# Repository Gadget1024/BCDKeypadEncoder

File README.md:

# BCDKeypadEncoder
 BCD Keypad encoder for Roger Hampson

Hardware and Software by Rob Barter (Bedrock Systems Limited)

KiCAD schematics and PCB Layout
Micro PIC16F1847 C++ Code

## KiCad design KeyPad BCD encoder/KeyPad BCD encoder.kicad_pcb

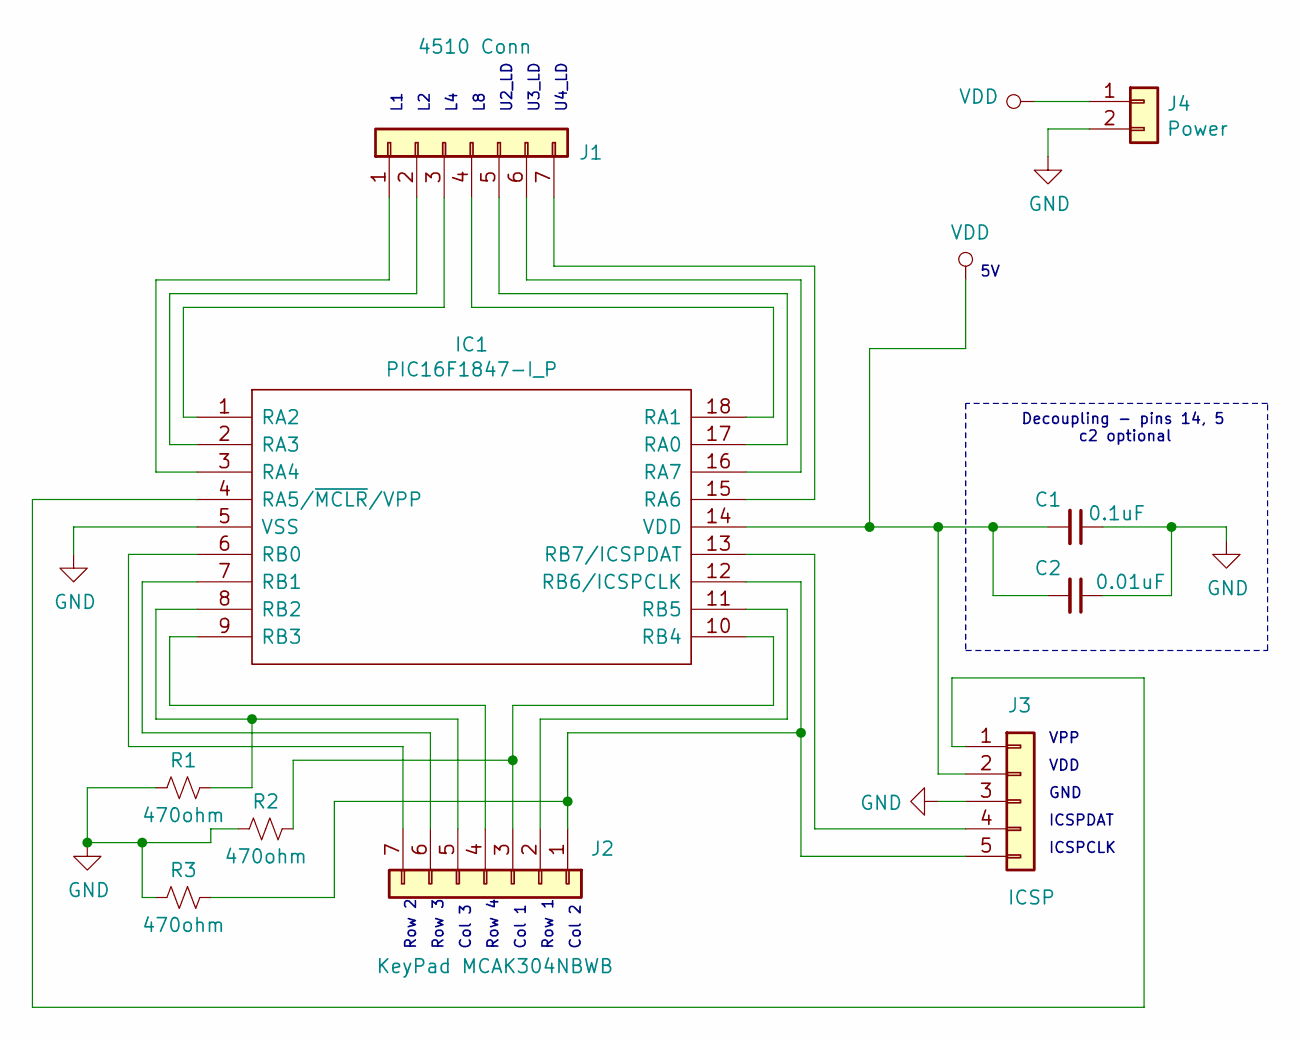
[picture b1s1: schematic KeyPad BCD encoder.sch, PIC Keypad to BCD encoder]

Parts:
C1: 0.1uF; C_1206_3216Metric_Pad1.42x1.75mm_HandSolder
C2: 0.01uF; C_1206_3216Metric_Pad1.42x1.75mm_HandSolder
IC1: PIC16F1847-I_P; SOIC-18W_7.5x11.6mm_P1.27mm; Mouser Part Number 579-PIC16F1847-I/P
J1: 4510 Conn; PinHeader_1x07_P2.54mm_Vertical
J2: KeyPad MCAK304NBWB; PinHeader_1x07_P2.54mm_Vertical
J3: ICSP; PinHeader_1x05_P2.54mm_Vertical
J4: Power; PinHeader_1x02_P2.54mm_Vertical
R1, R2, R3: 470ohm; R_0805_2012Metric_Pad1.15x1.40mm_HandSolder

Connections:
GND: C1.1, C2.1, IC1.5 (VSS), J3.3, J4.2, R1.2, R2.2, R3.2
unnamed: IC1.1 (RA2), J1.3
unnamed: IC1.2 (RA3), J1.2
unnamed: IC1.3 (RA4), J1.1
unnamed: IC1.4 (RA5/~MCLR~/VPP), J3.1
unnamed: IC1.6 (RB0), J2.7
unnamed: IC1.7 (RB1), J2.6
unnamed: IC1.8 (RB2), J2.5, R1.1
unnamed: IC1.9 (RB3), J2.4
unnamed: IC1.10 (RB4), J2.3, R2.1
unnamed: IC1.11 (RB5), J2.2
unnamed: IC1.12 (RB6/ICSPCLK), J2.1, J3.5, R3.1
unnamed: IC1.13 (RB7/ICSPDAT), J3.4
unnamed: IC1.15 (RA6), J1.7
unnamed: IC1.16 (RA7), J1.6
unnamed: IC1.17 (RA0), J1.5
unnamed: IC1.18 (RA1), J1.4
VDD: C1.2, C2.2, IC1.14 (VDD), J3.2, J4.1

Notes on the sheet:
Col 2
Row 1
Col 1
Row 4
Col 3
Row 3
Row 2
U4_LD
U3_LD
U2_LD
VPP
VDD
GND
ICSPDAT
ICSPCLK
Decoupling - pins 14, 5 c2 optional

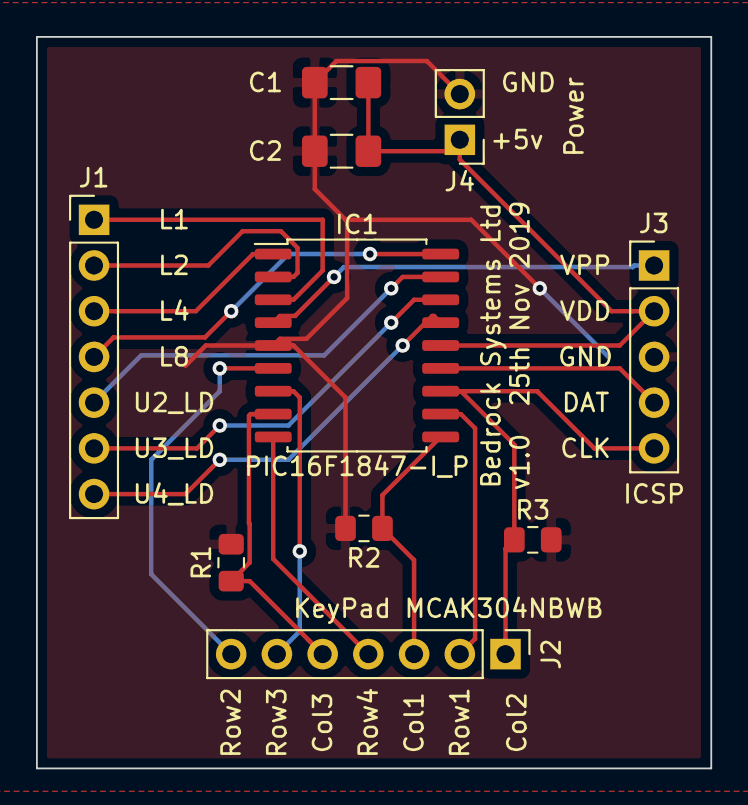
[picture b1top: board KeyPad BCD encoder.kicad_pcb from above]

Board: 2 copper layers, 37.5 x 40.6 mm, 10 parts (0 on the bottom side), 18 nets.

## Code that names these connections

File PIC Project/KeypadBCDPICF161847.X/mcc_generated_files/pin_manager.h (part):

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// get/set U2_LD_4510 aliases
#define U2_LD_4510_TRIS                 TRISAbits.TRISA0
#define U2_LD_4510_LAT                  LATAbits.LATA0
#define U2_LD_4510_PORT                 PORTAbits.RA0
#define U2_LD_4510_ANS                  ANSELAbits.ANSA0
#define U2_LD_4510_SetHigh()            do { LATAbits.LATA0 = 1; } while(0)
#define U2_LD_4510_SetLow()             do { LATAbits.LATA0 = 0; } while(0)
#define U2_LD_4510_Toggle()             do { LATAbits.LATA0 = ~LATAbits.LATA0; } while(0)
#define U2_LD_4510_GetValue()           PORTAbits.RA0
#define U2_LD_4510_SetDigitalInput()    do { TRISAbits.TRISA0 = 1; } while(0)
#define U2_LD_4510_SetDigitalOutput()   do { TRISAbits.TRISA0 = 0; } while(0)
#define U2_LD_4510_SetAnalogMode()      do { ANSELAbits.ANSA0 = 1; } while(0)
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// get/set L8_4510 aliases
#define L8_4510_TRIS                 TRISAbits.TRISA1
#define L8_4510_LAT                  LATAbits.LATA1
#define L8_4510_PORT                 PORTAbits.RA1
#define L8_4510_ANS                  ANSELAbits.ANSA1
#define L8_4510_SetHigh()            do { LATAbits.LATA1 = 1; } while(0)
#define L8_4510_SetLow()             do { LATAbits.LATA1 = 0; } while(0)
#define L8_4510_Toggle()             do { LATAbits.LATA1 = ~LATAbits.LATA1; } while(0)
#define L8_4510_GetValue()           PORTAbits.RA1
#define L8_4510_SetDigitalInput()    do { TRISAbits.TRISA1 = 1; } while(0)
#define L8_4510_SetDigitalOutput()   do { TRISAbits.TRISA1 = 0; } while(0)
#define L8_4510_SetAnalogMode()      do { ANSELAbits.ANSA1 = 1; } while(0)
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// get/set L4_4510 aliases
#define L4_4510_TRIS                 TRISAbits.TRISA2
#define L4_4510_LAT                  LATAbits.LATA2
#define L4_4510_PORT                 PORTAbits.RA2
#define L4_4510_ANS                  ANSELAbits.ANSA2
#define L4_4510_SetHigh()            do { LATAbits.LATA2 = 1; } while(0)
#define L4_4510_SetLow()             do { LATAbits.LATA2 = 0; } while(0)
#define L4_4510_Toggle()             do { LATAbits.LATA2 = ~LATAbits.LATA2; } while(0)
#define L4_4510_GetValue()           PORTAbits.RA2
#define L4_4510_SetDigitalInput()    do { TRISAbits.TRISA2 = 1; } while(0)
#define L4_4510_SetDigitalOutput()   do { TRISAbits.TRISA2 = 0; } while(0)
#define L4_4510_SetAnalogMode()      do { ANSELAbits.ANSA2 = 1; } while(0)
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// get/set L2_4510 aliases
#define L2_4510_TRIS                 TRISAbits.TRISA3
#define L2_4510_LAT                  LATAbits.LATA3
#define L2_4510_PORT                 PORTAbits.RA3
#define L2_4510_ANS                  ANSELAbits.ANSA3
#define L2_4510_SetHigh()            do { LATAbits.LATA3 = 1; } while(0)
#define L2_4510_SetLow()             do { LATAbits.LATA3 = 0; } while(0)
#define L2_4510_Toggle()             do { LATAbits.LATA3 = ~LATAbits.LATA3; } while(0)
#define L2_4510_GetValue()           PORTAbits.RA3
#define L2_4510_SetDigitalInput()    do { TRISAbits.TRISA3 = 1; } while(0)
#define L2_4510_SetDigitalOutput()   do { TRISAbits.TRISA3 = 0; } while(0)
#define L2_4510_SetAnalogMode()      do { ANSELAbits.ANSA3 = 1; } while(0)
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// get/set L1_4510 aliases
#define L1_4510_TRIS                 TRISAbits.TRISA4
#define L1_4510_LAT                  LATAbits.LATA4
#define L1_4510_PORT                 PORTAbits.RA4
#define L1_4510_ANS                  ANSELAbits.ANSA4
#define L1_4510_SetHigh()            do { LATAbits.LATA4 = 1; } while(0)
#define L1_4510_SetLow()             do { LATAbits.LATA4 = 0; } while(0)
#define L1_4510_Toggle()             do { LATAbits.LATA4 = ~LATAbits.LATA4; } while(0)
#define L1_4510_GetValue()           PORTAbits.RA4
#define L1_4510_SetDigitalInput()    do { TRISAbits.TRISA4 = 1; } while(0)
#define L1_4510_SetDigitalOutput()   do { TRISAbits.TRISA4 = 0; } while(0)
#define L1_4510_SetAnalogMode()      do { ANSELAbits.ANSA4 = 1; } while(0)
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// get/set U4_LD_4510 aliases
#define U4_LD_4510_TRIS                 TRISAbits.TRISA6
#define U4_LD_4510_LAT                  LATAbits.LATA6
#define U4_LD_4510_PORT                 PORTAbits.RA6
#define U4_LD_4510_SetHigh()            do { LATAbits.LATA6 = 1; } while(0)
#define U4_LD_4510_SetLow()             do { LATAbits.LATA6 = 0; } while(0)
#define U4_LD_4510_Toggle()             do { LATAbits.LATA6 = ~LATAbits.LATA6; } while(0)
#define U4_LD_4510_GetValue()           PORTAbits.RA6
#define U4_LD_4510_SetDigitalInput()    do { TRISAbits.TRISA6 = 1; } while(0)
#define U4_LD_4510_SetDigitalOutput()   do { TRISAbits.TRISA6 = 0; } while(0)

// get/set U3_LD_4510 aliases
#define U3_LD_4510_TRIS                 TRISAbits.TRISA7
#define U3_LD_4510_LAT                  LATAbits.LATA7
#define U3_LD_4510_PORT                 PORTAbits.RA7
#define U3_LD_4510_SetHigh()            do { LATAbits.LATA7 = 1; } while(0)
#define U3_LD_4510_SetLow()             do { LATAbits.LATA7 = 0; } while(0)
#define U3_LD_4510_Toggle()             do { LATAbits.LATA7 = ~LATAbits.LATA7; } while(0)
#define U3_LD_4510_GetValue()           PORTAbits.RA7
#define U3_LD_4510_SetDigitalInput()    do { TRISAbits.TRISA7 = 1; } while(0)
#define U3_LD_4510_SetDigitalOutput()   do { TRISAbits.TRISA7 = 0; } while(0)

// get/set ROW2 aliases
#define ROW2_TRIS                 TRISBbits.TRISB0
#define ROW2_LAT                  LATBbits.LATB0
#define ROW2_PORT                 PORTBbits.RB0
#define ROW2_WPU                  WPUBbits.WPUB0
#define ROW2_SetHigh()            do { LATBbits.LATB0 = 1; } while(0)
#define ROW2_SetLow()             do { LATBbits.LATB0 = 0; } while(0)
#define ROW2_Toggle()             do { LATBbits.LATB0 = ~LATBbits.LATB0; } while(0)
#define ROW2_GetValue()           PORTBbits.RB0
#define ROW2_SetDigitalInput()    do { TRISBbits.TRISB0 = 1; } while(0)
#define ROW2_SetDigitalOutput()   do { TRISBbits.TRISB0 = 0; } while(0)
#define ROW2_SetPullup()          do { WPUBbits.WPUB0 = 1; } while(0)
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// get/set ROW3 aliases
#define ROW3_TRIS                 TRISBbits.TRISB1
#define ROW3_LAT                  LATBbits.LATB1
#define ROW3_PORT                 PORTBbits.RB1
#define ROW3_WPU                  WPUBbits.WPUB1
#define ROW3_ANS                  ANSELBbits.ANSB1
#define ROW3_SetHigh()            do { LATBbits.LATB1 = 1; } while(0)
#define ROW3_SetLow()             do { LATBbits.LATB1 = 0; } while(0)
#define ROW3_Toggle()             do { LATBbits.LATB1 = ~LATBbits.LATB1; } while(0)
#define ROW3_GetValue()           PORTBbits.RB1
#define ROW3_SetDigitalInput()    do { TRISBbits.TRISB1 = 1; } while(0)
#define ROW3_SetDigitalOutput()   do { TRISBbits.TRISB1 = 0; } while(0)
#define ROW3_SetPullup()          do { WPUBbits.WPUB1 = 1; } while(0)
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// get/set COL3 aliases
#define COL3_TRIS                 TRISBbits.TRISB2
#define COL3_LAT                  LATBbits.LATB2
#define COL3_PORT                 PORTBbits.RB2
#define COL3_WPU                  WPUBbits.WPUB2
#define COL3_ANS                  ANSELBbits.ANSB2
#define COL3_SetHigh()            do { LATBbits.LATB2 = 1; } while(0)
#define COL3_SetLow()             do { LATBbits.LATB2 = 0; } while(0)
#define COL3_Toggle()             do { LATBbits.LATB2 = ~LATBbits.LATB2; } while(0)
#define COL3_GetValue()           PORTBbits.RB2
#define COL3_SetDigitalInput()    do { TRISBbits.TRISB2 = 1; } while(0)
#define COL3_SetDigitalOutput()   do { TRISBbits.TRISB2 = 0; } while(0)
#define COL3_SetPullup()          do { WPUBbits.WPUB2 = 1; } while(0)
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// get/set ROW4 aliases
#define ROW4_TRIS                 TRISBbits.TRISB3
#define ROW4_LAT                  LATBbits.LATB3
#define ROW4_PORT                 PORTBbits.RB3
#define ROW4_WPU                  WPUBbits.WPUB3
#define ROW4_ANS                  ANSELBbits.ANSB3
#define ROW4_SetHigh()            do { LATBbits.LATB3 = 1; } while(0)
#define ROW4_SetLow()             do { LATBbits.LATB3 = 0; } while(0)
#define ROW4_Toggle()             do { LATBbits.LATB3 = ~LATBbits.LATB3; } while(0)
#define ROW4_GetValue()           PORTBbits.RB3
#define ROW4_SetDigitalInput()    do { TRISBbits.TRISB3 = 1; } while(0)
#define ROW4_SetDigitalOutput()   do { TRISBbits.TRISB3 = 0; } while(0)
#define ROW4_SetPullup()          do { WPUBbits.WPUB3 = 1; } while(0)
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// get/set COL1 aliases
#define COL1_TRIS                 TRISBbits.TRISB4
#define COL1_LAT                  LATBbits.LATB4
#define COL1_PORT                 PORTBbits.RB4
#define COL1_WPU                  WPUBbits.WPUB4
#define COL1_ANS                  ANSELBbits.ANSB4
#define COL1_SetHigh()            do { LATBbits.LATB4 = 1; } while(0)
#define COL1_SetLow()             do { LATBbits.LATB4 = 0; } while(0)
#define COL1_Toggle()             do { LATBbits.LATB4 = ~LATBbits.LATB4; } while(0)
#define COL1_GetValue()           PORTBbits.RB4
#define COL1_SetDigitalInput()    do { TRISBbits.TRISB4 = 1; } while(0)
#define COL1_SetDigitalOutput()   do { TRISBbits.TRISB4 = 0; } while(0)
#define COL1_SetPullup()          do { WPUBbits.WPUB4 = 1; } while(0)
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// get/set ROW1 aliases
#define ROW1_TRIS                 TRISBbits.TRISB5
#define ROW1_LAT                  LATBbits.LATB5
#define ROW1_PORT                 PORTBbits.RB5
#define ROW1_WPU                  WPUBbits.WPUB5
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
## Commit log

2020-02-10 1st Release
    First release to Roger

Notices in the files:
PIC Project/KeypadBCDPICF161847.X/mcc_generated_files/pin_manager.h:
(c) 2018 Microchip Technology Inc. and its subsidiaries.
